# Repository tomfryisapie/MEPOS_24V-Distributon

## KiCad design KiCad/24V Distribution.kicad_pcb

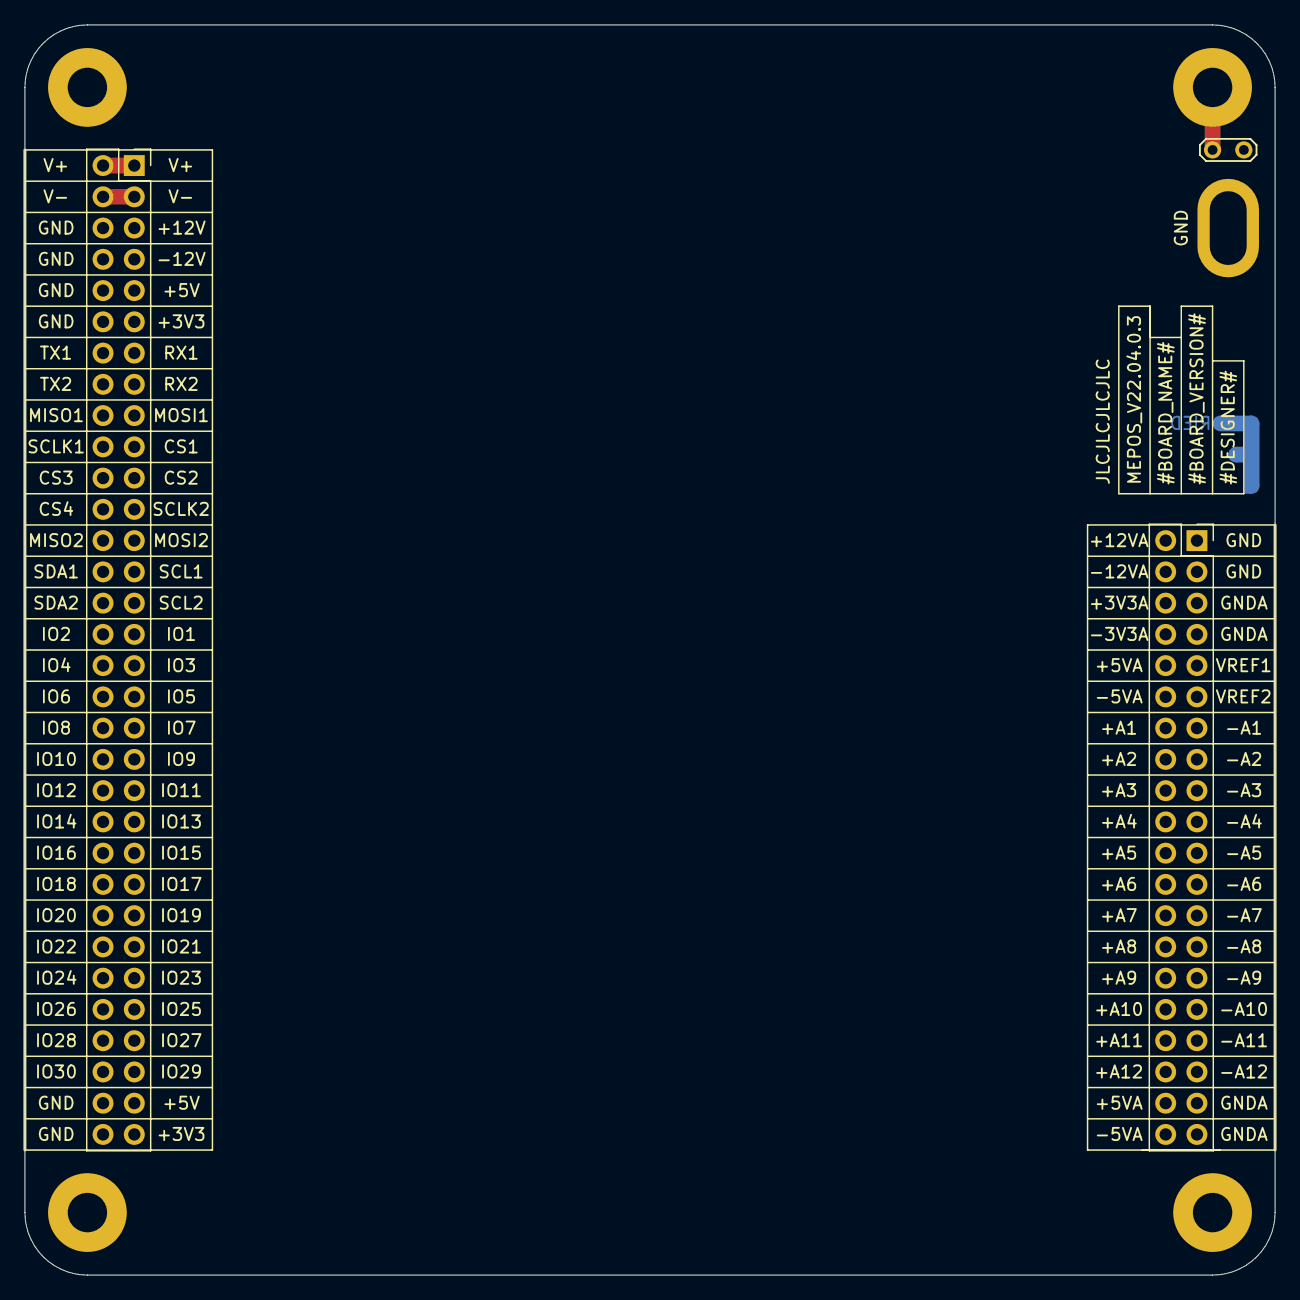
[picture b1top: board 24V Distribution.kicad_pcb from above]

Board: 4 copper layers, 101.6 x 101.6 mm, 9 parts (1 on the bottom side), 9 nets.

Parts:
GND201: Scope GND; Scope_GND
H201, H202, H203, H204: M3 Mount; MountingHole_3.2mm_M3_Pad
J201: Conn_02x32_Odd_Even; PinSocket_2x32_P2.54mm_Vertical
J202: Conn_02x20_Odd_Even; PinSocket_2x20_P2.54mm_Vertical
JP201: GND Jumper; TestPoint_2Pads_Pitch2.54mm_Drill0.8mm
KiCad_Logo: KiCad-Logo2_5mm_SilkScreen

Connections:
+3V3: J201.11, J201.63
+5V: J201.9, J201.61
+5VA: J202.10, J202.38
-5VA: J202.12, J202.40
AGND: J202.5, J202.7, J202.37, J202.39
GND: GND201.1, J201.6, J201.8, J201.10, J201.12, J201.62, J201.64, J202.1, J202.3, JP201.2
unnamed: H204.1, JP201.1
V+: J201.1, J201.2
V-: J201.3, J201.4

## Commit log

2022-03-12 Created KiCad Files
2022-03-13 Updated PCB and schematic and changed datasheet
2022-04-07 Updated to MEPOS V0.2
    updated pcb
2022-04-14 Updated to MEPOS V0.3
